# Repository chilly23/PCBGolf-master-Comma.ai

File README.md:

# PCBGolf — Compact Board Studies

PCB layout studies based on comma.ai's PCBGolf challenge. This repository contains reference files, EasyEDA projects, KiCad conversions, BOMs, and mechanical models.

The image above belongs to the upstream challenge material. It does not show a checked final submission from this repository.

## Project status

**The later design studies are incomplete. Do not treat them as fabrication-ready boards.**

[PARALLEL_DESIGN_STATUS.md](Rev%20B/PARALLEL_DESIGN_STATUS.md) records 239 unconnected connections in its selected four-layer study.
It also describes an unrouted two-layer placement. Neither study has a checked competition score.
Several status files refer to local `design/` and `work/` paths that are absent from this checkout.

## Reference system

The upstream reference combines these functions:

- A 12 V input with 5 V and 3.3 V supplies.
- Four OBD-C ports with controlled power and current monitoring.
- Four CAN transceivers and ignition simulation circuits.
- A USB hub and USB-C host connection.
- An STM32H725 microcontroller, microSD slot, button, and indicators.

Package substitutions and routing differ between revisions. Read each revision's notes before comparing the designs.

## Repository map

| Directory | Contents |
|---|---|
| [Rev 0](Rev%200/) | Upstream-style KiCad reference, libraries, STEP models, BOMs, and EasyEDA/Altium material |
| [Rev A](Rev%20A/) | Conversion and submission handoff artifacts |
| [Rev B](Rev%20B/) | EasyEDA handoffs, deliverables, BOMs, and routing-status reports |

Start with these engineering records:

- [Design status](Rev%20B/DESIGN_STATUS.md)
- [Four-layer status](Rev%20B/FOUR_LAYER_STATUS.md)
- [Routing studies](Rev%20B/ROUTING_STUDIES.md)
- [Saved parallel-design status](Rev%20B/PARALLEL_DESIGN_STATUS.md)
- [Rev A conversion instructions](Rev%20A/submission/KiCad%20files%20submission%20-%20Velan/READ-ME.txt)

## Open the design files

1. Select the revision you need.
2. Read its status and handoff notes.
3. Open `.kicad_pro` files with a compatible KiCad installation.
4. Import `.epro` or `.epro2` files with EasyEDA Pro or a compatible importer.
5. Check symbol and footprint libraries before changing the design.
6. Open STEP files in a mechanical CAD viewer.

Rev A requires a manual EasyEDA Pro project import for its native KiCad schematic and project.
Its supplied PCB conversion does not constitute a finalized submission.

## Review before fabrication

Complete routing, ERC, DRC, power-path analysis, thermal review, USB pair design, and mechanical checks.
Check connector access and component voltage ratings. Synchronize the schematic, PCB, BOM, and assembly model.

The challenge score combines assembled bounding-box volume, via count, and copper-layer count.
A bare-board outline alone cannot establish that score. The repository does not establish a current leaderboard position.

## Attribution and license

The reference design comes from [commaai/PCBGolf](https://github.com/commaai/PCBGolf).
[MIT](LICENSE) covers new documentation and eligible original contributions by Velan E.
It does not relicense the upstream board, supplied designs, challenge artwork, or third-party models.

The bundled KiCad library notice specifies CC-BY-SA 4.0 with a design-use exception.
Read [LICENSING.md](LICENSING.md) and the [original library notice](Rev%200/pcbgolf.3dshapes/KICAD_LIBRARY_LICENSE.md).

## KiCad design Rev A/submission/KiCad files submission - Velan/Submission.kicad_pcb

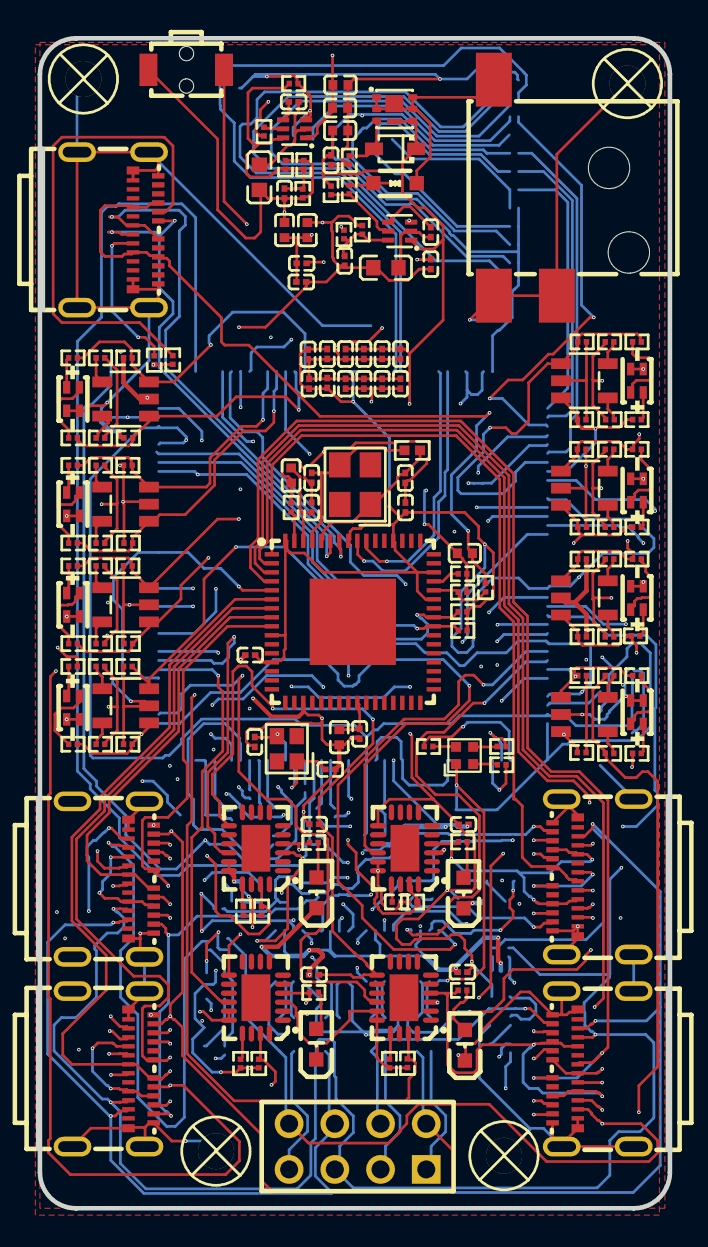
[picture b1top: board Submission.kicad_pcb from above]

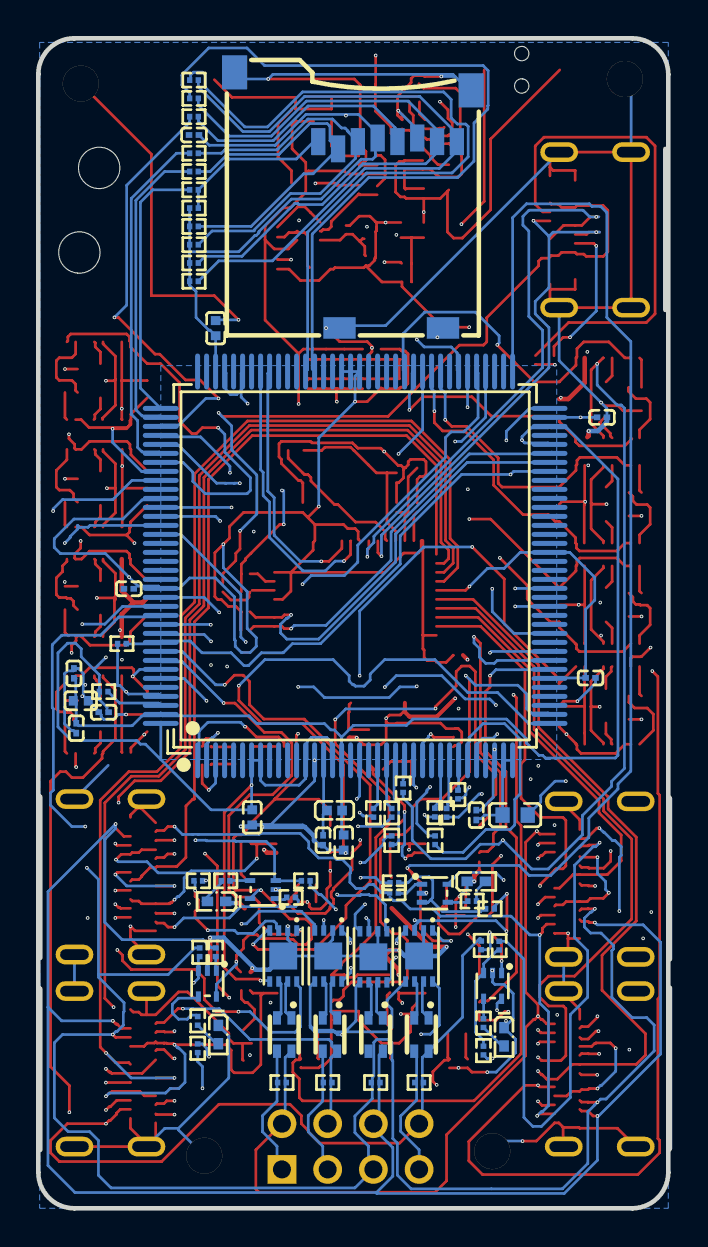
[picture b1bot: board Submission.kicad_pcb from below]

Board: 4 copper layers, 35.0 x 65.0 mm, 243 parts (74 on the bottom side), 191 nets.

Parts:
C1, C2, C7, C8, C13, C30, C31, C37, C39, C48, C49, C52: C0402
C3, C4, C5, C6, C9, C10, C11, C12, C14, C15, C16, C17, C18, C19, C20, C21, C22, C23, C24, C25, C26, C27, C28, C29, C32, C33, C34, C35, C36, C38, C40, C41, C42, C43, C44, C45, C46, C47, C50, C51, C53: C0201
D1: SOD-323_L1.8-W1.3-LS2.5-RD
D2: SOD-323_L1.7-W1.3-LS2.5-BI
J1: DC-IN-SMD_DC-044D-2.5A-2.0-SMT
J2: HDR-TH_8P-P2.54_SSW-104-23-F-D
L1, L2, L8: L0603
L3, L4, L5, L6: FILTER-SMD_4P-L2.0-W1.2-TL_ACM2012E
L7: L0402
LED1, LED2, LED3, LED4: LED0402-RD_RED
LED5, LED6, LED7, LED8, LED9, LED10, LED11, LED12: LED-SMD_L1.6-W0.8_HSMF-C163
LED13, LED14, LED15, LED16: LED0603-R-RD_RED
LED17: LED-SMD_TZ1615RGB3U-COMMON-YANG
Q1: DFN-6_L2.0-W2.0-P0.65-BL-EP-1
Q2, Q3, Q4, Q5, Q6, Q7, Q8, Q9: SOT-23-5_L2.9-W1.6-P0.95-LS2.8-TL
R1, R2, R3, R4, R5, R6, R7, R8, R9, R10, R11, R12, R13, R14, R15, R16, R17, R18, R19, R20, R21, R22, R23, R24, R25, R26, R27, R28, R29, R30, R31, R32, R33, R34, R35, R36, R37, R38, R39, R40, R41, R42, R43, R44, R45, R46, R47, R48, R49, R50, R51, R52, R53, R54, R55, R56, R57, R58, R59, R60, R61, R62, R63, R64, R65, R66, R67, R68, R69, R70, R71, R72, R73, R74, R75, R76, R77, R78, R79, R80, R81, R82, R83, R84, R85, R86, R87, R88, R89, R90, R91, R92, R93, R94, R95, R96, R97, R98, R99, R100, R101, R102, R103, R104, R105, R106, R107, R108, R109, R110, R111, R112, R113, R114, R115, R116, R117, R119, R120, R121, R122, R123: R0201
R118: R0402
SCREW1, SCREW2, SCREW3, SCREW4: Screw-Hole-M2
SW1: SW-SMD_L3.9-W2.9-LS4.8SWQC_SPST
U1, U2: SOT-563-6_L1.6-W1.2-P0.50-LS1.6-BL
U3, U4, U5, U6: TDFN-8_L3.0-W2.0-P0.50-TL-EP
U7, U8, U9, U10: SOT-553-5_L1.6-W1.2-P0.50-LS1.6-BL
U11, U16, U17, U18: WQFN-20_L4.0-W3.0-P0.50-BL-EP
U12, U13, U14, U15, U23: USB-SMD_USB4081-03-A
U19: QFN-64_L9.0-W9.0-P0.50-BL-EP4.8
U20: CRYSTAL-SMD_4P-L3.2-W2.5-BL
U21: LQFP-144_L20.0-W20.0-P0.50-LS22.0-BL
U22: MICRO-SD-SMD_XDTP-1001-098
X1: CRYSTAL-SMD_4P-L2.0-W1.6-BL

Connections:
$1N1259: D1.2, Q1.3, R5.1
$1N1313: D2.1, J1.3, Q1.1, Q1.2, Q1.5, Q1.6, Q1.7
$1N13203: LED5.1, R36.1
$1N13246: Q2.5, R33.1
$1N13260: Q2.4, R34.1
$1N13283: R79.1, U11.17
$1N13322: LED13.1, R81.1
$1N13324: LED5.2, R35.1
$1N16078: R16.2, R17.1, U7.3
$1N16234: LED1.2, R18.2
$1N24572: R105.1, R110.1, U22.8
$1N24631: R106.1, R111.1, U22.1
$1N24642: R107.1, R112.1, U22.2
$1N24649: R114.1, U22.5
$1N24659: R104.1, R109.1, U22.7
$1N24671: R108.1, R113.1, U22.3
$1N24731: C5.2, L1.1, U1.2
$1N24732: C5.1, U1.4
$1N24733: C4.1, R1.1, R2.1, U1.6
$1N24736: R3.1, R4.2, U1.5
$1N24745: C11.2, L2.1, U2.2
$1N24746: C11.1, U2.4
$1N24747: C10.1, R6.1, R7.1, R8.1, R9.2, U2.6
$1N24748: R10.1, U2.5
$1N24760: L3.2, U3.6
$1N24761: L3.1, U3.7
$1N24762: L4.1, U4.7
$1N24763: L4.2, U4.6
$1N24773: L5.1, U5.7
$1N24774: L5.2, U5.6
$1N24784: L6.1, U6.7
$1N24785: L6.2, U6.6
$1N24845: R15.2, U7.1
$1N24848: R18.1, U7.4
$1N24879: R22.1, U8.4
$1N24882: R19.2, U8.1
$1N24886: LED2.2, R22.2
$1N24888: R20.2, R21.1, U8.3
$1N24889: R26.1, U9.4
$1N24890: R30.1, U10.4
$1N24895: R23.2, U9.1
$1N24896: R27.2, U10.1
$1N24903: LED4.2, R30.2
$1N24904: LED3.2, R26.2
$1N24907: R28.2, R29.1, U10.3
$1N24908: R24.2, R25.1, U9.3
$1N24946: LED6.2, R38.1
$1N24947: Q3.4, R41.1
$1N24948: Q3.5, R40.1
$1N24949: LED6.1, R39.1
$1N24959: LED7.2, R43.1
$1N24960: Q4.4, R46.1
$1N24961: Q4.5, R45.1
$1N24962: LED7.1, R44.1
$1N24972: LED8.2, R49.1
$1N24973: Q5.4, R52.1
$1N24974: Q5.5, R51.1
$1N24975: LED8.1, R50.1
$1N25006: LED12.2, R73.1
$1N25007: LED11.2, R67.1
$1N25008: LED10.2, R61.1
$1N25009: LED9.2, R55.1
$1N25010: Q7.4, R64.1
$1N25011: Q9.4, R76.1
$1N25012: Q8.4, R70.1
$1N25013: Q6.4, R58.1
$1N25014: Q7.5, R63.1
$1N25015: Q9.5, R75.1
$1N25016: Q8.5, R69.1
$1N25017: Q6.5, R57.1
$1N25018: LED10.1, R62.1
$1N25019: LED12.1, R74.1
$1N25020: LED11.1, R68.1
$1N25021: LED9.1, R56.1
$1N25057: R81.2, U11.4, U12.A4, U12.A9, U12.B4, U12.B9
$1N25065: R84.2, U13.A4, U13.A9, U13.B4, U13.B9, U16.4
$1N25090: LED14.1, R84.1
$1N25091: R83.1, U16.17
$1N25094: R90.2, U15.A4, U15.A9, U15.B4, U15.B9, U18.4
$1N25095: R87.2, U14.A4, U14.A9, U14.B4, U14.B9, U17.4
$1N25144: LED16.1, R90.1
$1N25145: LED15.1, R87.1
$1N25146: R89.1, U18.17
$1N25147: R86.1, U17.17
$1N25148: LED17.4, R93.1
$1N25149: LED17.3, R92.1
$1N25150: LED17.2, R91.2
$1N25179: R94.1, U21.28
$1N25180: R95.1, U21.29
$1N25181: R96.1, U21.30
$1N25182: R97.1, U21.31
$1N25226: R98.1, U21.21
$1N25227: R99.1, U21.22
$1N25228: R100.1, U21.23
$1N25229: R101.1, U21.24
$1N25245: R102.1, U21.142
$1N25293: R115.1, U23.A5
$1N25294: R116.2, U23.B5
$1N25317: R117.1, U19.63
$1N25319: C53.1, R118.1, U19.60, U20.1
$1N25320: C45.1, R118.2, U19.61, U20.3
$1N25323: R119.2, U19.45
$1N25345: C49.2, C50.2, U19.25
+3V3: C8.2, C9.1, C10.2, C15.2, C18.2, C21.2, C24.2, C30.2, C31.2, C32.2, C33.2, C34.2, C35.2, C44.2, C46.2, C47.2, L2.2, L8.1, LED17.1, R6.2, R7.2, R8.2, R102.2, R104.2, R105.2, R106.2, R107.2, R108.2, R120.1, R121.1, SW1.1, U3.5, U4.5, U5.5, U6.5, U19.5, U19.10, U19.13, U19.43, U19.46, U19.52, U19.57, U19.64, U21.7, U21.8, U21.13, U21.16, U21.19, U21.32, U21.42, U21.56, U21.71, U21.79, U21.90, U21.91, U21.92, U21.106, U21.119, U21.129, U21.144, U22.4
+5V: C1.2, C2.2, C3.1, C4.2, C12.1, C13.2, C14.2, C17.2, C20.2, C23.2, L1.2, R1.2, R10.2, R17.2, R21.2, R25.2, R29.2, U2.1, U3.3, U4.3, U5.3, U6.3
+12V: C6.1, C7.2, C16.2, C19.2, C22.2, C25.2, C26.2, C27.2, C28.2, C29.2, D1.1, Q1.4, Q1.8, R4.1, U1.1, U7.5, U8.5, U9.5, U10.5, U11.11, U16.11, U17.11, U18.11
BTN: R103.2, SW1.2, U21.65, U21.135
CAN0_EN: U3.8, U21.134
CAN0_H: J2.2, L3.4, R11.2, R15.1, U12.A2, U13.A2, U14.A2, U15.A2
CAN0_L: J2.1, L3.3, R11.1, R16.1, U12.A3, U13.A3, U14.A3, U15.A3
CAN0_RX: U3.4, U21.136
CAN0_TX: U3.1, U21.137
CAN1_EN: U4.8, U21.130
CAN1_H: J2.4, L4.4, R12.2, R19.1, U12.A11, U13.A11, U14.A11, U15.A11
CAN1_L: J2.3, L4.3, R12.1, R20.1, U12.A10, U13.A10, U14.A10, U15.A10
CAN1_RX: U4.4, U21.132
CAN1_TX: U4.1, U21.133
CAN2_EN: U5.8, U21.121
CAN2_H: J2.6, L5.4, R13.2, R23.1, U12.B2, U13.B2, U14.B2, U15.B2
CAN2_L: J2.5, L5.3, R13.1, R24.1, U12.B3, U13.B3, U14.B3, U15.B3
CAN2_RX: U5.4, U21.123
CAN2_TX: U5.1, U21.122
CAN3_EN: U6.8, U21.131
CAN3_H: J2.8, L6.4, R14.2, R27.1, U12.B11, U13.B11, U14.B11, U15.B11
CAN3_L: J2.7, L6.3, R14.1, R28.1, U12.B10, U13.B10, U14.B10, U15.B10
CAN3_RX: U6.4, U21.72
CAN3_TX: U6.1, U21.73
CH1_D_N: U12.A7, U12.B7, U19.1
CH1_D_P: U12.A6, U12.B6, U19.2
CH1_IMON: R80.1, U11.19, U21.47
CH1_PWR_EN: U11.14, U21.37
CH1_SBU1: R33.2, R34.2, R96.2, U12.A8
CH1_SBU1_IGN: Q2.1, R31.2, R36.2, U21.112
CH1_SBU1_RELAY: Q2.3, R32.2, R35.2, U21.113
CH1_SBU2: R57.2, R58.2, R97.2, U12.B8
CH1_SBU2_IGN: Q6.1, R56.2, R59.2, U21.115
CH1_SBU2_RELAY: Q6.3, R55.2, R60.2, U21.116
CH2_D_N: U13.A7, U13.B7, U19.3
CH2_D_P: U13.A6, U13.B6, U19.4
CH2_IMON: R82.1, U16.19, U21.50
CH2_PWR_EN: U16.14, U21.38
CH2_SBU1: R40.2, R41.2, R100.2, U13.A8
CH2_SBU1_IGN: Q3.1, R37.2, R39.2, U21.117
CH2_SBU1_RELAY: Q3.3, R38.2, R42.2, U21.120
CH2_SBU2: R63.2, R64.2, R98.2, U13.B8
CH2_SBU2_IGN: Q7.1, R62.2, R65.2, U21.76
CH2_SBU2_RELAY: Q7.3, R61.2, R66.2, U21.78
CH3_D_N: U14.A7, U14.B7, U19.6
CH3_D_P: U14.A6, U14.B6, U19.7
CH3_IMON: R85.1, U17.19, U21.52
CH3_PWR_EN: U17.14, U21.43
CH3_SBU1: R45.2, R46.2, R94.2, U14.A8
CH3_SBU1_IGN: Q4.1, R44.2, R47.2, U21.82
CH3_SBU1_RELAY: Q4.3, R43.2, R48.2, U21.81
CH3_SBU2: R69.2, R70.2, R95.2, U14.B8
CH3_SBU2_IGN: Q8.1, R68.2, R71.2, U21.77
CH3_SBU2_RELAY: Q8.3, R67.2, R72.2, U21.83
CH4_D_N: U15.A7, U15.B7, U19.8
CH4_D_P: U15.A6, U15.B6, U19.9
CH4_IMON: R88.1, U18.19, U21.45
CH4_PWR_EN: U18.14, U21.44
CH4_SBU1: R51.2, R52.2, R101.2, U15.A8
CH4_SBU1_IGN: Q5.1, R50.2, R53.2, U21.84
CH4_SBU1_RELAY: Q5.3, R49.2, R54.2, U21.85
CH4_SBU2: R75.2, R76.2, R99.2, U15.B8
CH4_SBU2_IGN: Q9.1, R74.2, R77.2, U21.138
CH4_SBU2_RELAY: Q9.3, R73.2, R78.2, U21.139
GND: C1.1, C2.1, C3.2, C6.2, C7.1, C8.1, C9.2, C12.2, C13.1, C14.1, C15.1, C16.1, C17.1, C18.1, C19.1, C20.1, C21.1, C22.1, C23.1, C24.1, C25.1, C26.1, C27.1, C28.1, C29.1, C30.1, C31.1, C32.1, C33.1, C34.1, C35.1, C36.1, C37.1, C38.2, C39.1, C40.1, C41.1, C42.2, C43.1, C45.2, C46.1, C47.1, C48.1, C49.1, C50.1, C51.1, C52.1, C53.2, D2.2, J1.4, J1.5, LED1.1, LED2.1, LED3.1, LED4.1, LED5.3, LED5.4, LED6.3, LED6.4, LED7.3, LED7.4, LED8.3, LED8.4, LED9.3, LED9.4, LED10.3, LED10.4, LED11.3, LED11.4, LED12.3, LED12.4, LED13.2, LED14.2, LED15.2, LED16.2, Q2.2, Q3.2, Q4.2, Q5.2, Q6.2, Q7.2, Q8.2, Q9.2, R2.2, R3.2, R5.2, R9.1, R31.1, R32.1, R37.1, R42.1, R47.1, R48.1, R53.1, R54.1, R59.1, R60.1, R65.1, R66.1, R71.1, R72.1, R77.1, R78.1, R79.2, R80.2, R82.2, R83.2, R85.2, R86.2, R88.2, R89.2, R103.1, R115.2, R116.1, R117.2, R119.1, R123.2, SCREW1.1, SCREW2.1, SCREW3.1, SCREW4.1, U1.3, U2.3, U3.2, U3.9, U4.2, U4.9, U5.2, U5.9, U6.2, U6.9, U7.2, U8.2, U9.2, U10.2, U11.3, U11.15, U11.16, U12.1, U12.2, U12.3, U12.4, U12.5, U12.6, U12.A1, U12.A12, U12.B12, U13.1, U13.2, U13.3, U13.4, U13.5, U13.6, U13.A1, U13.A12, U13.B12, U14.1, U14.2, U14.3, U14.4, U14.5, U14.6, U14.A1, U14.A12, U14.B12, U15.1, U15.2, U15.3, U15.4, U15.5, U15.6, U15.A1, U15.A12, U15.B12, U16.3, U16.15, U16.16, U17.3, U17.15, U17.16, U18.3, U18.15, U18.16, U19.19, U21.14, U21.34, U21.141, U22.6, U22.10, U23.1, U23.2, U23.3, U23.4, U23.5, U23.6, U23.A1, U23.A12, U23.B1, U23.B12
HUB_SCL: R120.2, U19.41, U21.66
HUB_SDA: R121.2, U19.40, U21.67
LED_B: R93.2, U21.1
LED_G: R92.2, U21.2
LED_R: R91.1, U21.3
PH0: C42.1, U21.25, X1.1
PH1: C43.2, U21.26, X1.3
SD_CLK: R114.2, U21.111
SD_CMD: R113.2, U21.114
SD_D0: R109.2, U21.95
SD_D1: R110.2, U21.96
SD_D2: R111.2, U21.109
SD_D3: R112.2, U21.110
STM_D_N: U19.55, U21.100
STM_D_P: U19.56, U21.101
USB_D_N: U19.58, U23.A7, U23.B7
USB_D_P: U19.59, U23.A6, U23.B6
VBUS: C48.2, R122.1, U23.A4, U23.A9, U23.B4, U23.B9
VBUS_DET: R122.2, R123.1, U19.44
VDD18PLL: C51.2, C52.2, U19.62
VDDA: C36.2, L8.2, U21.35, U21.36
VDDLDO: C37.2, C39.2, C40.2, C41.2, L7.1, U21.17, U21.68, U21.70, U21.103, U21.105, U21.143
VLXSMPS: C38.1, L7.2, U21.15
